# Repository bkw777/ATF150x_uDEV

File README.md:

# ATF150x_uDEV

Tiny dev board for Atmel/Microchip ATF1502 & ATF1504 TQFP-44.

[v016 PCB at OSHPark](https://oshpark.com/shared_projects/1EtYH37r)

For C1-C4 use anything from 0.22u to 1u.

JTAG pin 6 may optionally be connected to IC pin 38 (OE1#/VPP) by the VPP solder jumper.  
[ATF150x_uPRG](https://github.com/bkw777/ATF150x_uPRG) has a matching option to output 12v VPP on JTAG pin 6.  
<!-- 
VPP is only needed if the chip is currently programmed with gateware that disables jtag.  
NOTE: VPP does NOT overcome the secure programming option!  
-->

# Programming
[Buckle Up!](programming.md)

<!--

https://github.com/hoglet67/atf15xx_yosys

https://github.com/roscopeco/atfprog-tools

https://github.com/hackup/ATF2FT232HQ

https://snowgoons.ro/posts/2020-11-25-atf15xx-vhdl-development-for-cheap/

https://www.eevblog.com/forum/fpga/atmel-atf150x-cpld-and-wincupl/

https://www.eevblog.com/forum/microcontrollers/freeopen-source-alternative-to-wincupl/

http://forum.6502.org/viewtopic.php?f=10&t=7920

dev kit
https://www.digikey.com/en/products/detail/microchip-technology/ATF15XX-DK3-U/5235981

prochip license 2 years $840
https://www.digikey.com/en/products/detail/microchip-technology/ATDS15XXKSW1/1596666

prochip cd $300 maybe just the cd same as the download? functional? not?
https://www.digikey.com/en/products/detail/microchip-technology/ATDS1500PC/524057?s=N4IgTCBcDaIA4CcD2BjAFgSziAugXyA

-->

# Credits
Modified originally from [whitequark/ATF15xx-EVB](https://github.com/whitequark/ATF15xx-EVB)

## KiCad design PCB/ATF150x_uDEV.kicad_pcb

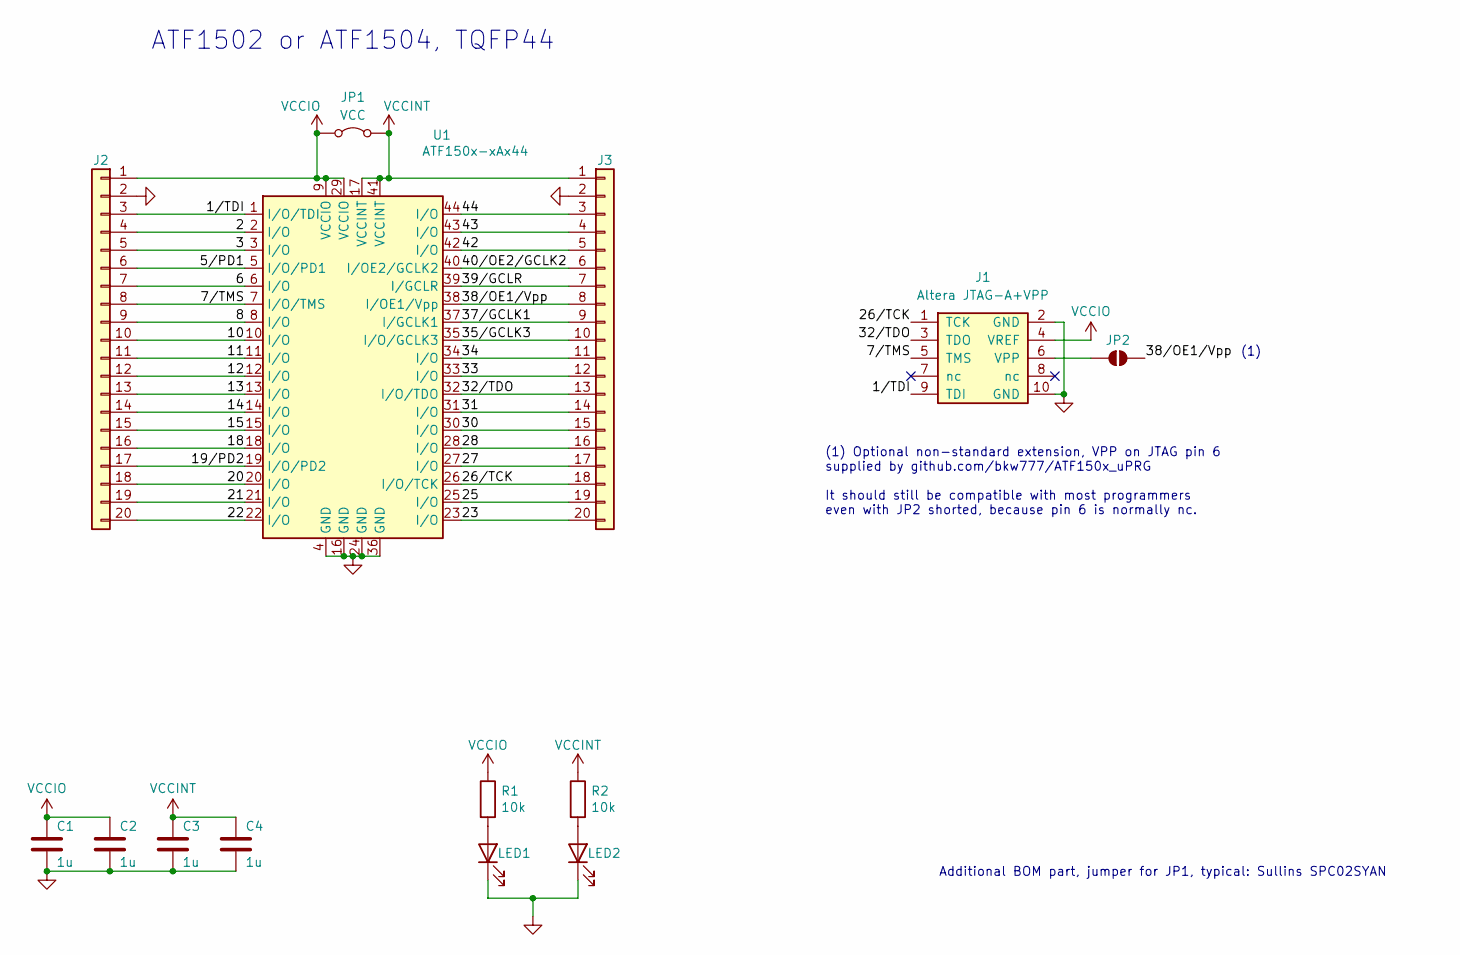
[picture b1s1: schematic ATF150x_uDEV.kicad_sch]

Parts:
C1, C2, C3, C4: 1u; C_0805; MPN CL21B105KOFNNWE
J1: Altera JTAG-A+VPP; IDC-Header_2x05_P2.54mm_Vertical; MPN SBH11-PBPC-D05-ST-BK
J2, J3: 1x20x2.54mm; PinHeader_1x20_P2.54mm_Vertical; MPN PRPC020SAAN-RC
JP1: VCC; PinHeader_1x02_P2.54mm_Horizontal; MPN PRPC002SBBN-M71RC
JP2: VPP; SolderJumper_1mm_2p_open
LED1, LED2: GRN; LED_0805; MPN LG_R971-KN-1-0-20-R18
R1, R2: 10k; R_0805; MPN RMCF0805FT10K0
U1: ATF150x-xAx44; VQFP44; MPN ATF1504ASL-25AU44

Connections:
/1/TDI: J1.9 (TDI), J2.3, U1.1 (I/O/TDI)
/2: J2.4, U1.2 (I/O)
/3: J2.5, U1.3 (I/O)
/5/PD1: J2.6, U1.5 (I/O/PD1)
/6: J2.7, U1.6 (I/O)
/7/TMS: J1.5 (TMS), J2.8, U1.7 (I/O/TMS)
/8: J2.9, U1.8 (I/O)
/10: J2.10, U1.10 (I/O)
/11: J2.11, U1.11 (I/O)
/12: J2.12, U1.12 (I/O)
/13: J2.13, U1.13 (I/O)
/14: J2.14, U1.14 (I/O)
/15: J2.15, U1.15 (I/O)
/18: J2.16, U1.18 (I/O)
/19/PD2: J2.17, U1.19 (I/O/PD2)
/20: J2.18, U1.20 (I/O)
/21: J2.19, U1.21 (I/O)
/22: J2.20, U1.22 (I/O)
/23: J3.20, U1.23 (I/O)
/25: J3.19, U1.25 (I/O)
/26/TCK: J1.1 (TCK), J3.18, U1.26 (I/O/TCK)
/27: J3.17, U1.27 (I/O)
/28: J3.16, U1.28 (I/O)
/30: J3.15, U1.30 (I/O)
/31: J3.14, U1.31 (I/O)
/32/TDO: J1.3 (TDO), J3.13, U1.32 (I/O/TDO)
/33: J3.12, U1.33 (I/O)
/34: J3.11, U1.34 (I/O)
/35/GCLK3: J3.10, U1.35 (I/O/GCLK3)
/37/GCLK1: J3.9, U1.37 (I/GCLK1)
/38/OE1/Vpp: J3.8, JP2.2 (B), U1.38 (I/OE1/Vpp)
/39/GCLR: J3.7, U1.39 (I/GCLR)
/40/OE2/GCLK2: J3.6, U1.40 (I/OE2/GCLK2)
/42: J3.5, U1.42 (I/O)
/43: J3.4, U1.43 (I/O)
/44: J3.3, U1.44 (I/O)
GND: C1.2, C2.2, C3.2, C4.2, J1.2 (GND), J1.10 (GND), J2.2, J3.2, LED1.1 (K), LED2.1 (K), U1.4 (GND), U1.16 (GND), U1.24 (GND), U1.36 (GND)
unnamed: J1.6 (VPP), JP2.1 (A)
unnamed: LED1.2 (A), R1.2
unnamed: LED2.2 (A), R2.2
VCCINT: C3.1, C4.1, J3.1, JP1.2 (B), R2.1, U1.17 (VCCINT), U1.41 (VCCINT)
VCCIO: C1.1, C2.1, J1.4 (VREF), J2.1, JP1.1 (A), R1.1, U1.9 (VCCIO), U1.29 (VCCIO)

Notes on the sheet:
(1)
ATF1502 or ATF1504, TQFP44
(1) Optional non-standard extension, VPP on JTAG pin 6 supplied by github.com/bkw777/ATF150x_uPRG It should still be compatible with most programmers even with JP2 shorted, because pin 6 is normally nc.
Additional BOM part, jumper for JP1, typical: Sullins SPC02SYAN

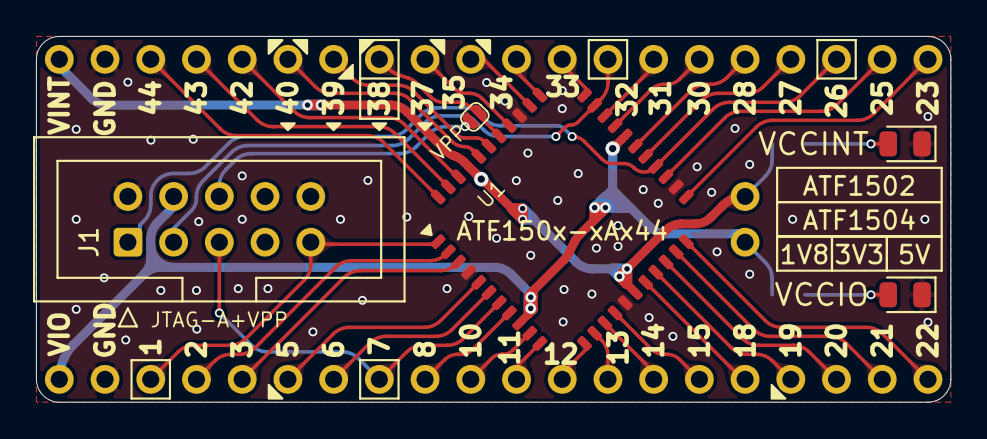
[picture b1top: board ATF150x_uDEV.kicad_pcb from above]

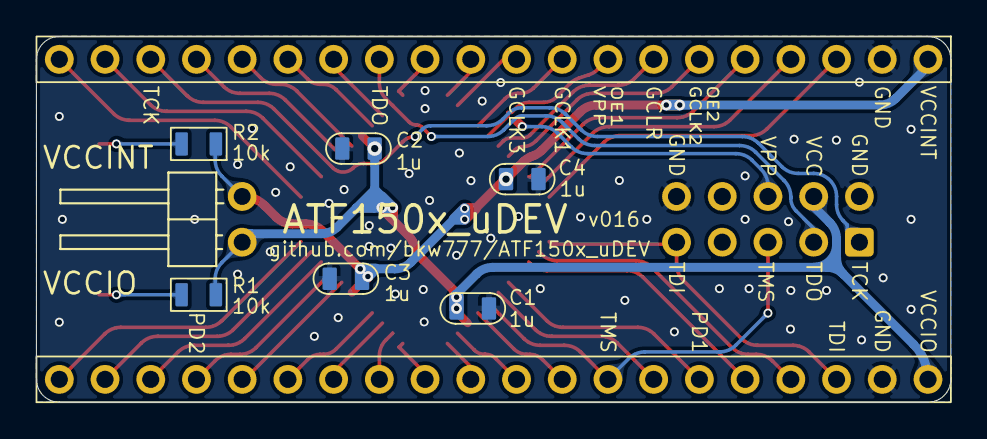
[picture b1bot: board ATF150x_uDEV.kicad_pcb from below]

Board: 2 copper layers, 50.8 x 20.3 mm, 14 parts (9 on the bottom side), 42 nets.

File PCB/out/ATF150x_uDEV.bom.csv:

"Reference","Value","Datasheet","Footprint","Qty","DNP"
"C1,C2,C3,C4","1u","datasheets/MLCC_2512.pdf","000_LOCAL:C_0805","4",""
"J1","Altera JTAG-A+VPP","datasheets/JTAG-A.pdf","000_LOCAL:IDC-Header_2x05_P2.54mm_Vertical","1",""
"J2,J3","1x20x2.54mm","~","000_LOCAL:PinHeader_1x20_P2.54mm_Vertical","2",""
"JP1","VCC","~","000_LOCAL:PinHeader_1x02_P2.54mm_Horizontal","1",""
"LED1,LED2","GRN","datasheets/LG_R971.pdf","000_LOCAL:LED_0805","2",""
"R1,R2","10k","datasheets/SEI-RMCF_RMCP.pdf","000_LOCAL:R_0805","2",""
"U1","ATF150x-xAx44","datasheets/ATF1502AS.pdf","000_LOCAL:VQFP44","1",""

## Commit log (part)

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2024-06-02 initial
2024-06-14 single board, silkscreen pin numbers
2024-06-14 readme
2024-06-14 shield all traces
2024-06-16 tiny alignment of fiducials
2024-06-20 notes in hidden comments in readme
2024-06-23 fix silkscreen pin 6, remove AS from name & part number
2024-06-24 jtag symbols
2024-06-24 add VPP to JTAG
2024-07-02 add programming software install & usage doc
2024-07-05 programming wrapper scripts
2024-07-10 rename oprg to atfsvf, hide wine messages
2024-07-10 change cupl to a wrapper to run 5vcomp instead of being a modified copy of 5vcomp
2024-07-10 programming.md
2024-07-10 atfsvf support ASV devices, ERASE_xxx.svf
2024-07-10 improve wine wrapper scripts
2024-07-11 silkscreen touchup
2024-07-13 move scripts into bin to avoid cupl CUPL collision on windows
2024-07-14 silkscreen and gnd paths
2024-07-24 scripts: WINEDEBUG, exec, comments
2024-07-25 atfsvf -c cfgcmd... , docs
2024-07-26 seperate vccio vccint
2024-07-26 move jumper to bottom side
2024-07-26 update link in comment in sch
2024-07-26 tiny pcb adjusts
2026-02-27 correct pin 44 label, silkscreen, pics, move vpp jumper
2026-03-17 pcb double vias on power traces

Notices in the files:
PCB/ATF150x_uDEV.kicad_pcb:
CC-BY-SA
